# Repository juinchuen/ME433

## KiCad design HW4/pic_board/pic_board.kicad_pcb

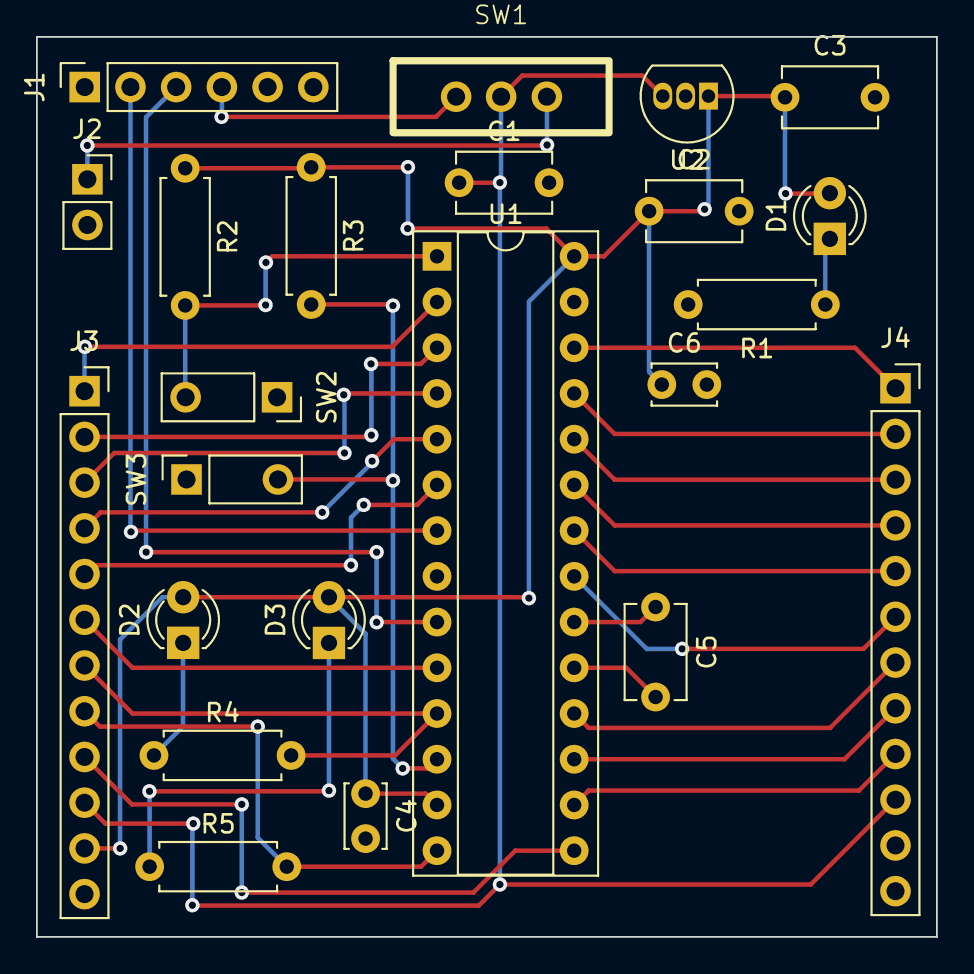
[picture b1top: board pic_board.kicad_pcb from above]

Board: 2 copper layers, 50.0 x 50.0 mm, 23 parts (0 on the bottom side), 31 nets.

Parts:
C1, C2, C3, C5: 1uF; C_Disc_D5.1mm_W3.2mm_P5.00mm
C4, C6: 0.1uF; C_Disc_D3.4mm_W2.1mm_P2.50mm
D1: LED; LED_D3.0mm
D2: GREEN; LED_D3.0mm
D3: YELLOW; LED_D3.0mm
J1: CP2102; PinSocket_1x06_P2.54mm_Vertical
J2: BATTERY; PinSocket_1x02_P2.54mm_Vertical
J3: LEFT; PinSocket_1x12_P2.54mm_Vertical
J4: RIGHT; PinSocket_1x12_P2.54mm_Vertical
R1, R4, R5: 330; R_Axial_DIN0207_L6.3mm_D2.5mm_P7.62mm_Horizontal
R2, R3: 10K; R_Axial_DIN0207_L6.3mm_D2.5mm_P7.62mm_Horizontal
SW1: SW_SLIDE; swslide
SW2: MCLR; push_button
SW3: USER; push_button
U1: DIP-28_W7.62mm_Socket
U2: AP7381; TO-92L_Inline

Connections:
+3.3V: C2.1, C3.1, C4.1, C6.1, D1.2 (A), D2.2 (A), D3.2 (A), J3.11, J4.11, R2.1, R3.1, U1.13 (V_{DD}), U1.28 (AV_{DD}), U2.1 (VO)
+5V: J1.4, SW1.1 (A)
/A0: J3.1, U1.2 (A0)
/A1: J3.2, U1.3 (A1)
/A3: J3.6, U1.10 (A3)
/B0: J3.3, U1.4 (B0)
/B1: J3.4, U1.5 (B1)
/B2: J3.5, U1.6 (B2)
/B6: J3.9, U1.15 (B6)
/B7: J4.9, U1.16 (B7)
/B8: J4.8, U1.17 (B8)
/B9: J4.7, U1.18 (B9)
/B10: J4.6, U1.21 (B10)
/B11: J4.5, U1.22 (B11)
/B12: J4.4, U1.23 (B12)
/B13: J4.3, U1.24 (B13)
/B14: J4.2, U1.25 (B14)
/B15: J4.1, U1.26 (B15)
/GREEN: J3.7, R4.2, U1.11 (B4)
/MCLR: R2.2, SW2.3 (B), U1.1 (~MCLR)
/U1RX: J1.3, U1.9 (A2)
/U1TX: J1.2, U1.7 (B3)
/USER: R3.2, U1.12 (A4)
/Vin: C1.1, J3.10, J4.10, SW1.2 (B), U2.3 (VI)
/YELLOW: J3.8, R5.2, U1.14 (B5)
GND: C1.2, C2.2, C3.2, C4.2, C5.2, C6.2, J1.6, J2.2, J3.12, J4.12, R1.2, SW2.1 (A), SW3.1 (A), SW3.2 (A), U1.8 (V_{SS}), U1.19 (V_{SS}), U1.27 (AV_{SS}), U2.2 (GND)
unnamed: D1.1 (K), R1.1
unnamed: D2.1 (K), R4.1
unnamed: D3.1 (K), R5.1
unnamed: J2.1, SW1.3 (C)
unnamed: C5.1, U1.20 (V_{CAP})

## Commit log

2023-04-05 added template files
2023-04-05 preliminary HW2
2023-04-05 HW2 complete
2023-04-06 HW3 does not work
2023-04-06 HW3 Works
2023-04-21 HW5 works
2023-04-26 HW6 done
2023-04-26 HW7 works
2023-05-09 HW8 Works
2023-05-09 HW9 complete
2023-05-26 HW10 Works
2023-05-30 HW11 works
2023-06-01 hw12 images
2023-06-03 HW15
